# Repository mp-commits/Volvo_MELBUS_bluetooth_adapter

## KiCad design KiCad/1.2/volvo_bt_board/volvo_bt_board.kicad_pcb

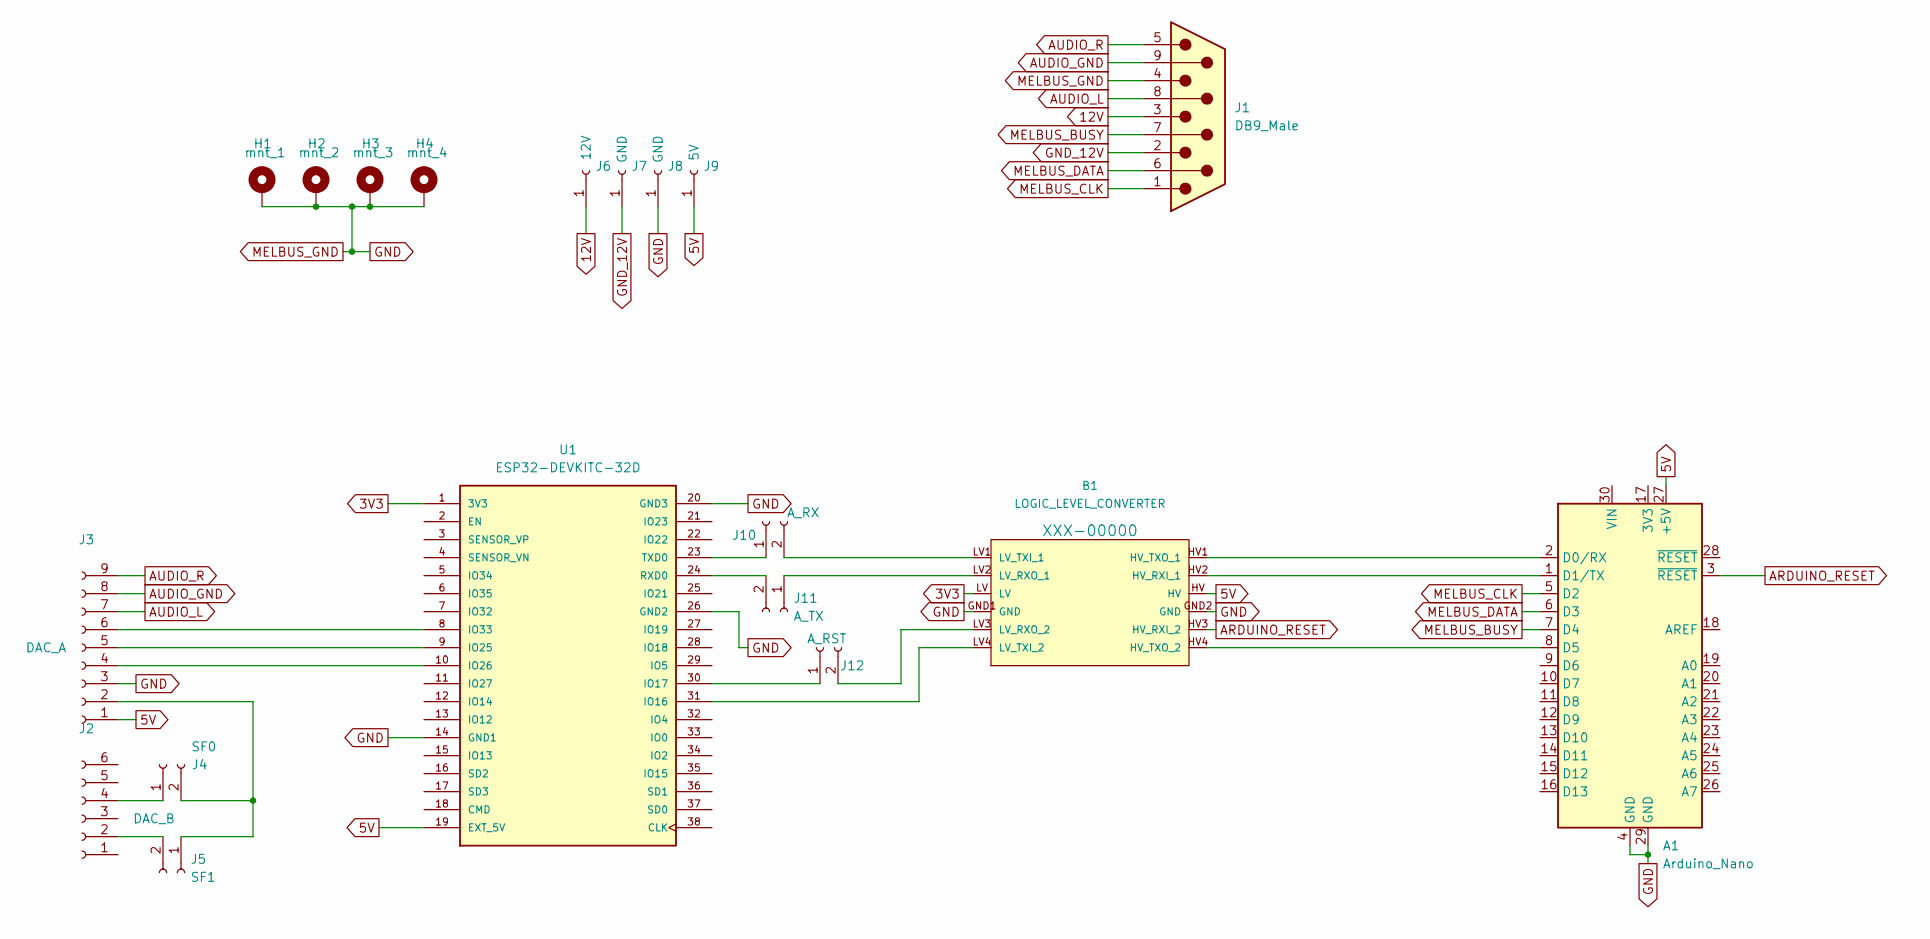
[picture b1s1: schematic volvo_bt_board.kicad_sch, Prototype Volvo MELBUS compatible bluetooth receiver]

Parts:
A1: Arduino_Nano
B1: LOGIC_LEVEL_CONVERTER; SPARKFUN_LOGIC_LEVEL_CONVERTER
H1: mnt_1; MountingHole_2.5mm_Pad
H2: mnt_2; MountingHole_2.5mm_Pad
H3: mnt_3; MountingHole_2.5mm_Pad
H4: mnt_4; MountingHole_2.5mm_Pad
J1: DB9_Male; DSUB-9_Male_Horizontal_P2.77x2.84mm_EdgePinOffset7.70mm_Hou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
J2: DAC_B; PinSocket_1x06_P2.54mm_Vertical
J3: DAC_A; PinSocket_1x09_P2.54mm_Vertical
J4: SF0; 1X02_NO_SILK
J5: SF1; 1X02_NO_SILK
J6: 12V; PinSocket_1x01_P2.54mm_Vertical
J7, J8: GND; PinSocket_1x01_P2.54mm_Vertical
J9: 5V; PinSocket_1x01_P2.54mm_Vertical
J10: A_RX; 1X02_NO_SILK
J11: A_TX; 1X02_NO_SILK
J12: A_RST; 1X02_NO_SILK
U1: ESP32-DEVKITC-32D; MODULE_ESP32-DEVKITC-32D; PARTREV 4

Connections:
3V3: B1.LV, U1.1 (3V3)
5V: A1.27 (+5V), B1.HV, J3.1, J9.1, U1.19 (EXT_5V)
12V: J1.3, J6.1
ARDUINO_RESET: A1.3 (~RESET), B1.HV3 (HV_RXI_2)
AUDIO_GND: J1.9, J3.8
AUDIO_L: J1.8, J3.7
AUDIO_R: J1.5, J3.9
GND: A1.4 (GND), A1.29 (GND), B1.GND1 (GND), B1.GND2 (GND), H1.1, H2.1, H3.1, H4.1, J1.4, J3.3, J8.1, U1.14 (GND1), U1.20 (GND3), U1.26 (GND2)
GND_12V: J1.2, J7.1
MELBUS_BUSY: A1.7 (D4), J1.7
MELBUS_CLK: A1.5 (D2), J1.1
MELBUS_DATA: A1.6 (D3), J1.6
unnamed: A1.1 (D1/TX), B1.HV2 (HV_RXI_1)
unnamed: A1.2 (D0/RX), B1.HV1 (HV_TXO_1)
unnamed: A1.8 (D5), B1.HV4 (HV_TXO_2)
unnamed: B1.LV1 (LV_TXI_1), J10.2
unnamed: B1.LV2 (LV_RXO_1), J11.1
unnamed: B1.LV3 (LV_RXO_2), J12.2
unnamed: B1.LV4 (LV_TXI_2), U1.31 (IO16)
unnamed: J2.2, J5.2
unnamed: J2.4, J4.1
unnamed: J3.2, J4.2, J5.1
unnamed: J3.4, U1.10 (IO26)
unnamed: J3.5, U1.9 (IO25)
unnamed: J3.6, U1.8 (IO33)
unnamed: J10.1, U1.23 (TXD0)
unnamed: J11.2, U1.24 (RXD0)
unnamed: J12.1, U1.30 (IO17)

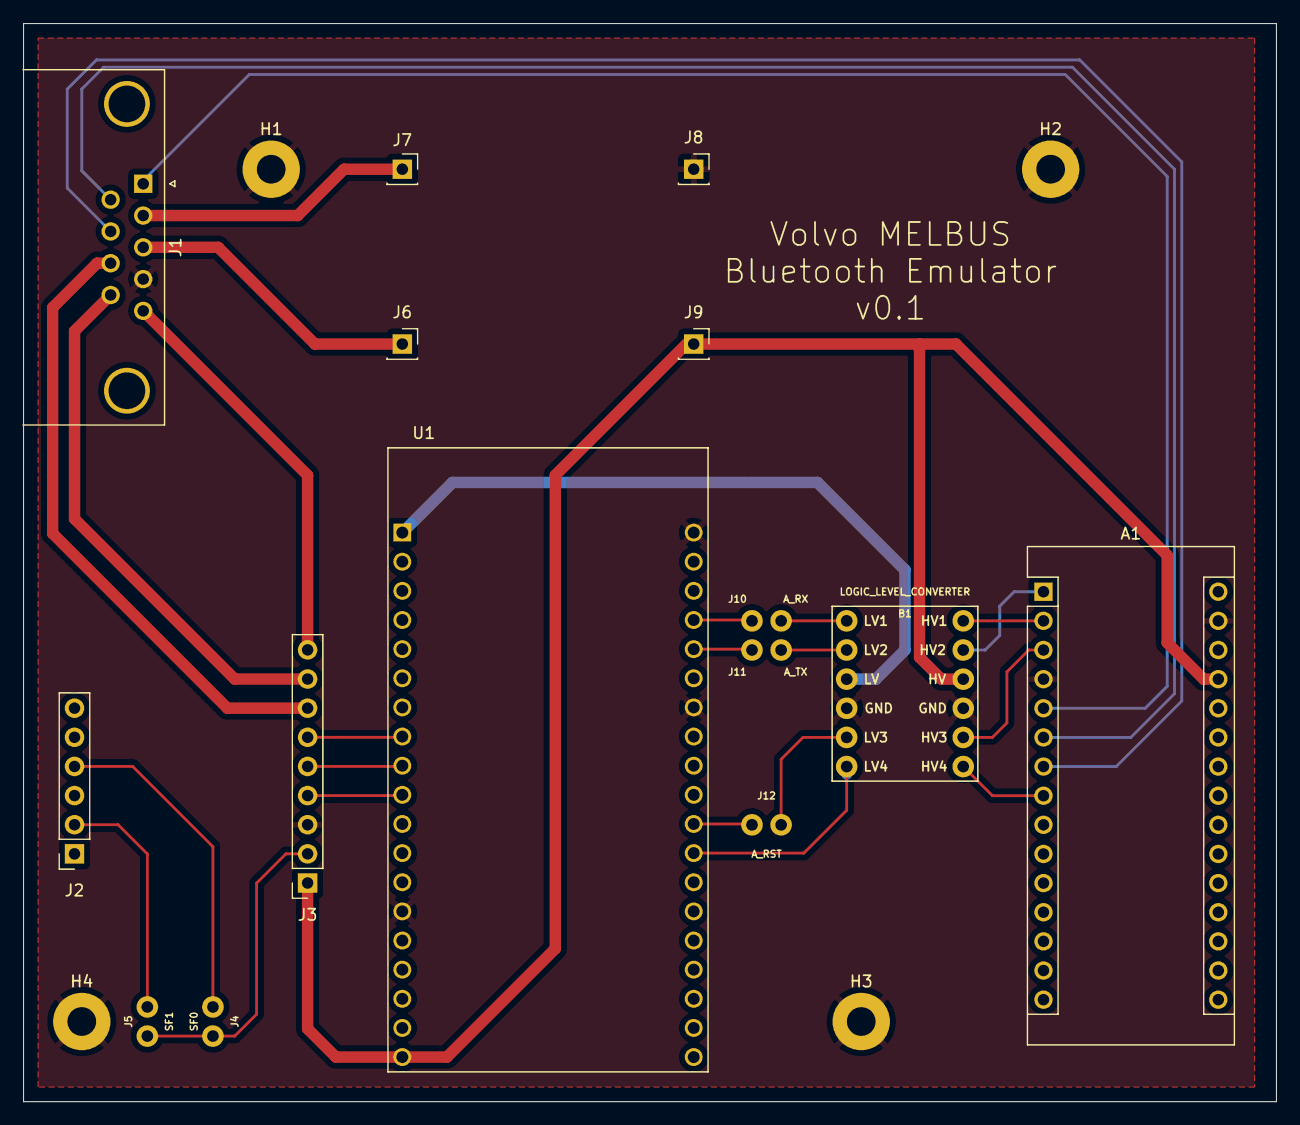
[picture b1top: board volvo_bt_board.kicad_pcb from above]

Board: 2 copper layers, 109.2 x 94.0 mm, 19 parts (0 on the bottom side), 28 nets.

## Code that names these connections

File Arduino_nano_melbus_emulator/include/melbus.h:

/**
 * @file melbus.h
 * @author Mikael Penttinen (mikael.penttinen3@gmail.com)
 * @brief Main header for the melbus component
 * @version 0.1
 * @date 2022-03-03
 * 
 * @copyright Copyright (c) 2022
 * 
 */

#ifndef MELBUS_H
#define MELBUS_H

#include <stdint.h>
#include <stdbool.h>

#define MELBUS_CLK_PIN 2
#define MELBUS_DATA_PIN 3
#define MELBUS_BUSY_PIN 4

typedef uint8_t MELBUS_byte_t;

bool MELBUS_Init();

void MELBUS_BeginBusyInit(void);

void MELBUS_SendByte(const MELBUS_byte_t byte);

uint32_t MELBUS_RxBytesAvailable(void);

MELBUS_byte_t MELBUS_ReadByte(void);

bool MELBUS_ConfirmSync(void);

#endif

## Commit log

2022-04-02 Import and refactor melbus library
2022-04-02 Add serial interface to send media commands
2022-04-02 Add esp32 receiver program
2022-04-02 Serial communication working
2022-04-02 Add media controller and i2s conf
2022-04-02 Add diagnostics messages for melbus init
2022-04-03 Add enable signal to control device init
2022-04-03 Add support for alive signal
2022-04-03 Update dac pins
2022-04-03 Add volume control
    - use preset knob for volume
2022-04-04 Add pcb version 1
2022-04-04 Update pcb, generate gerber
2022-04-08 Update project
2022-04-10 Add second better version of pcb
2022-04-10 Add jlcpcb zip
2022-04-10 Fix esp init logic
2022-04-20 Set appropriate default volume for dac
2022-04-20 Add non sync init confirmation
2022-04-23 Add support for fast forward and reverse
    - Add support for scanmode (not tested)
    - Add ack bytes for approriate commands
    - Add board version 1.2
2022-04-23 Add ff/fr to bt control
2022-04-24 Proper naming
2022-04-24 Add melbus sniffer
2022-05-05 Add random playback support with multiple ACRCP next
2022-05-07 Add fast version of the melbus receiver firmware
    This version of the melbus is based on the implementation by
    Karl Hagström and uses a hacky approach on reading the dataline
    at a falling edge
2022-05-07 Use 230400 baudrate
2022-05-07 Add support for metadata transmission
2022-05-07 Update gitignore
2022-05-19 WIP cleanup
